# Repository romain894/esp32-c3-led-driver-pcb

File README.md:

# ESP32-C3 Wi-Fi LED driver

PCB based on an ESP32-C3 super mini to control LED:

  - Wi-Fi
  - Up to 6 PWM channels with MOSFET
  - 3 analog inputs
  - 24-12V to 5V step down chip
  - Extension to add an IR remote
  - Possibility to add I2C peripherals
  - An extra MOSFET on a non-PWM channel (e.g. to control an ATX power supply)

v1.0: tests in progress

Romain THOMAS 2024

## PCB views

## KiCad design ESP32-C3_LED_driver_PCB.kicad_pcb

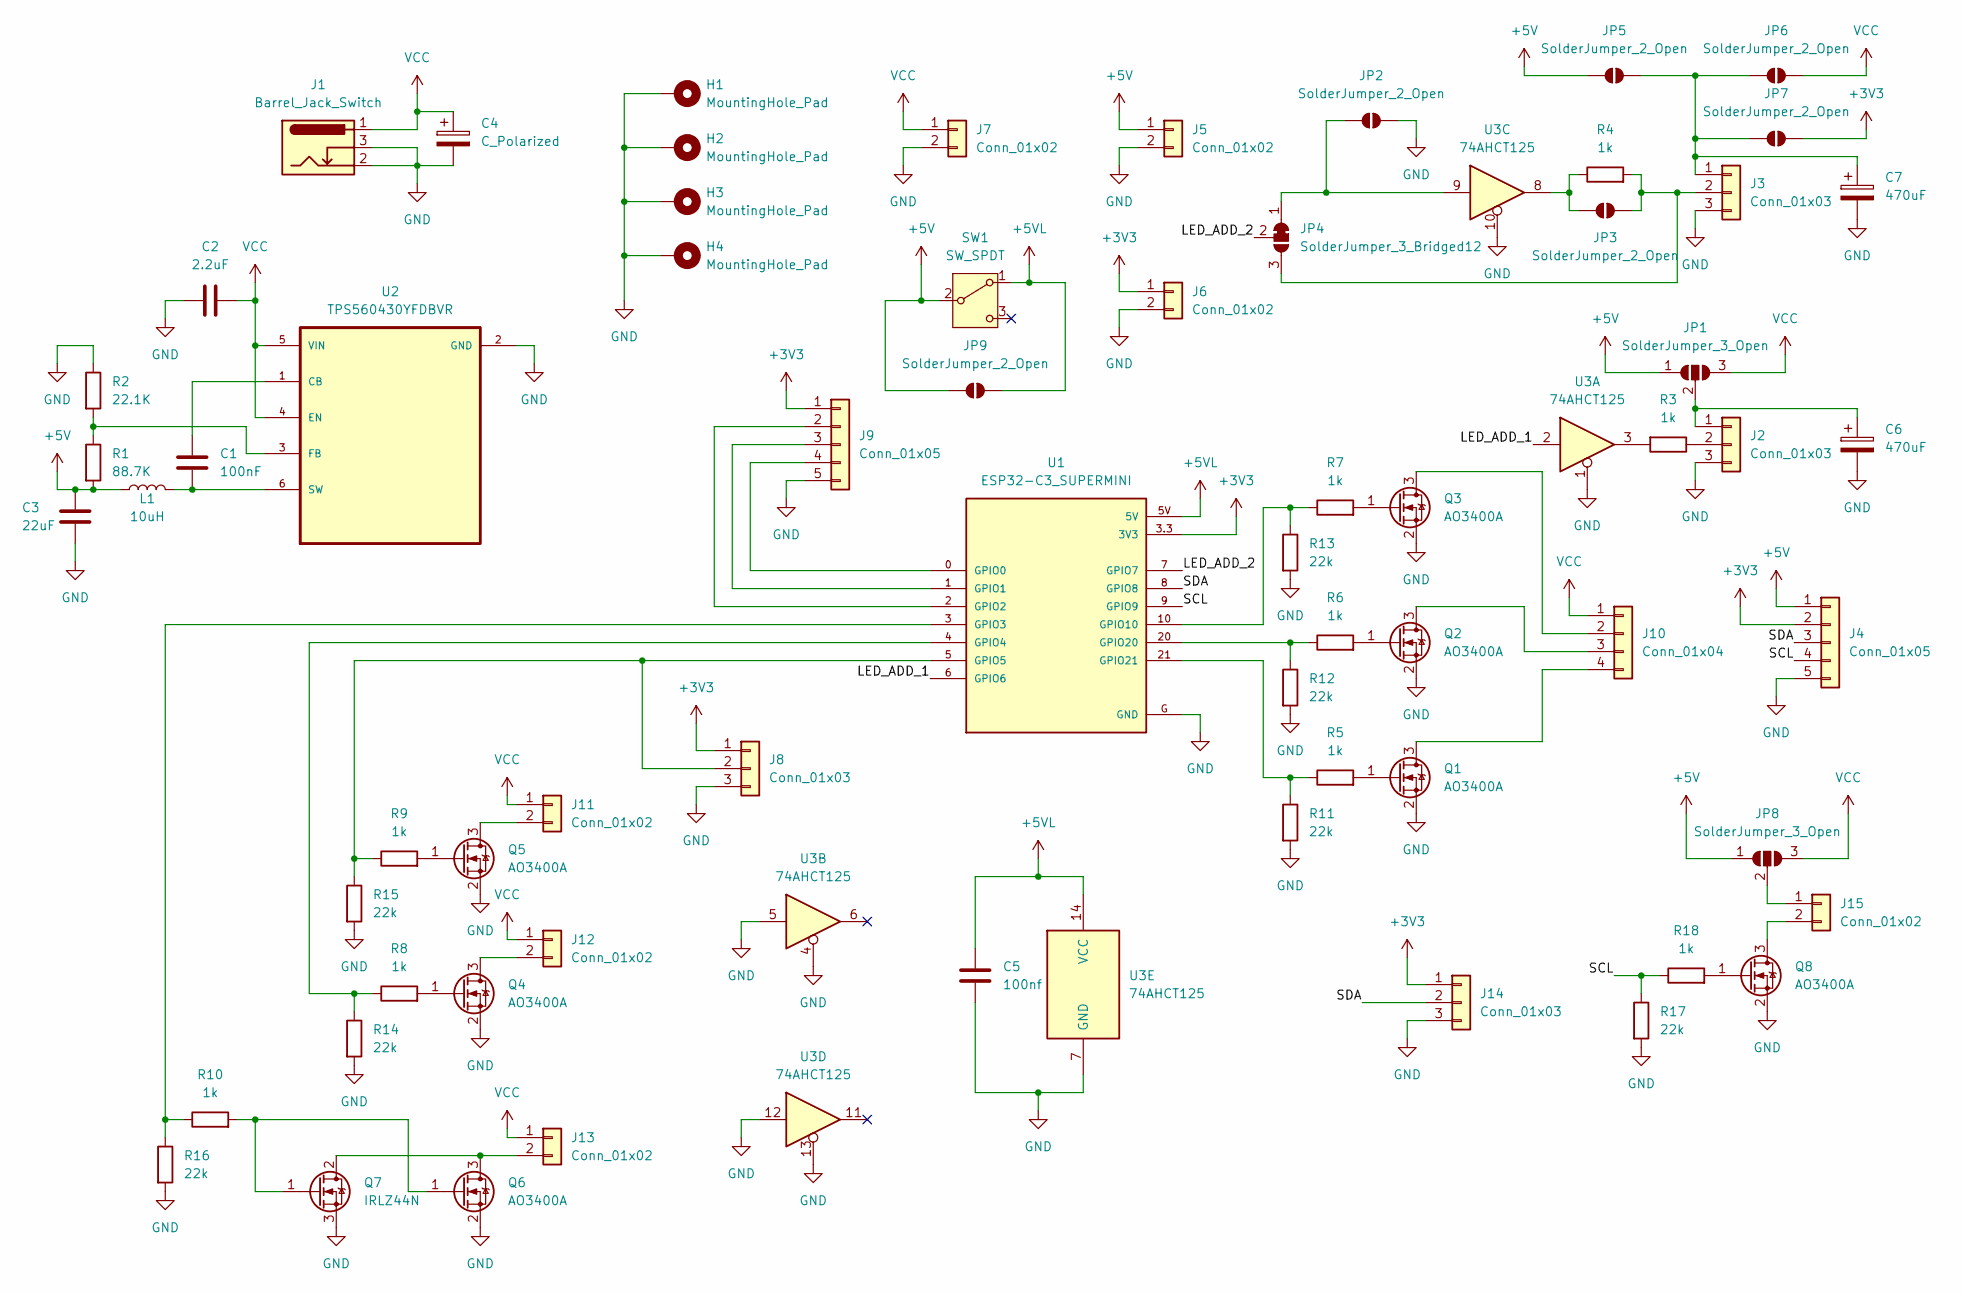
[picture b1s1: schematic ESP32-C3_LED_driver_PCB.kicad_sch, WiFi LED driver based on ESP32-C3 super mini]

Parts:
C1: 100nF; C_1206_3216Metric_Pad1.33x1.80mm_HandSolder
C2: 2.2uF; C_1206_3216Metric_Pad1.33x1.80mm_HandSolder
C3: 22uF; C_1206_3216Metric_Pad1.33x1.80mm_HandSolder
C4: C_Polarized; CP_Radial_D10.0mm_P2.50mm_P5.00mm
C5: 100nf; C_1206_3216Metric_Pad1.33x1.80mm_HandSolder
C6, C7: 470uF; CP_Radial_D10.0mm_P2.50mm_P5.00mm
H1, H2, H3, H4: MountingHole_Pad; MountingHole_3.5mm_Pad_Via
J1: Barrel_Jack_Switch; BarrelJack_Horizontal
J2, J3, J8, J14: Conn_01x03; JST_XH_B3B-XH-A_1x03_P2.50mm_Vertical
J4, J9: Conn_01x05; JST_XH_B5B-XH-A_1x05_P2.50mm_Vertical
J5, J6, J7, J11, J12, J13, J15: Conn_01x02; JST_XH_B2B-XH-A_1x02_P2.50mm_Vertical
J10: Conn_01x04; JST_XH_B4B-XH-A_1x04_P2.50mm_Vertical
JP1, JP8: SolderJumper_3_Open; SolderJumper-3_P1.3mm_Open_RoundedPad1.0x1.5mm
JP2, JP3, JP5, JP6, JP7, JP9: SolderJumper_2_Open; SolderJumper-2_P1.3mm_Open_RoundedPad1.0x1.5mm
JP4: SolderJumper_3_Bridged12; SolderJumper-3_P1.3mm_Bridged12_RoundedPad1.0x1.5mm
L1: 10uH; L_Chilisin_BMRA00040420
Q1, Q2, Q3, Q4, Q5, Q6, Q8: AO3400A; SOT-23
Q7: IRLZ44N; TO-220-3_Horizontal_TabDown
R1: 88.7K; R_1206_3216Metric_Pad1.30x1.75mm_HandSolder
R2: 22.1K; R_1206_3216Metric_Pad1.30x1.75mm_HandSolder
R3, R4, R5, R6, R7, R8, R9, R10, R18: 1k; R_1206_3216Metric_Pad1.30x1.75mm_HandSolder
R11, R12, R13, R14, R15, R16, R17: 22k; R_1206_3216Metric_Pad1.30x1.75mm_HandSolder
SW1: SW_SPDT; SW_Slide-03_Wuerth-WS-SLTV_10x2.5x6.4_P2.54mm
U1: ESP32-C3_SUPERMINI; MODULE_ESP32-C3_SUPERMINI
U2: TPS560430YFDBVR; SOT95P280X145-6N
U3: 74AHCT125; TSSOP-14_4.4x5mm_P0.65mm

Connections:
+3V3: J4.2, J6.1, J8.1, J9.1, J14.1, JP7.2 (B), U1.3.3 (3V3)
+5V: C3.1, J4.1, J5.1, JP1.1 (A), JP5.1 (A), JP8.1 (A), JP9.1 (A), L1.1, R1.2, SW1.2 (B)
+5VL: C5.1, JP9.2 (B), SW1.1 (A), U1.5V, U3.14 (VCC)
/LED_ADD_1: U1.6 (GPIO6), U3.2
/LED_ADD_2: JP4.2 (C), U1.7 (GPIO7)
/SCL: J4.4, R17.1, R18.1, U1.9 (GPIO9)
/SDA: J4.3, J14.2, U1.8 (GPIO8)
GND: C2.1, C3.2, C4.2, C5.2, C6.2, C7.2, H1.1, H2.1, H3.1, H4.1, J1.2, J1.3, J2.3, J3.3, J4.5, J5.2, J6.2, J7.2, J8.3, J9.5, J14.3, JP2.2 (B), Q1.2 (S), Q2.2 (S), Q3.2 (S), Q4.2 (S), Q5.2 (S), Q6.2 (S), Q7.3 (S), Q8.2 (S), R2.1, R11.2, R12.2, R13.2, R14.2, R15.2, R16.2, R17.2, U1.G (GND), U2.2 (GND), U3.1, U3.4, U3.5, U3.7 (GND), U3.10, U3.12, U3.13
unnamed: C6.1, J2.1, JP1.2 (C)
unnamed: J2.2, R3.1
unnamed: C7.1, J3.1, JP5.2 (B), JP6.1 (A), JP7.1 (A)
unnamed: J3.2, JP3.2 (B), JP4.3 (B), R4.2
unnamed: J8.2, R9.1, R15.1, U1.5 (GPIO5)
unnamed: J9.2, U1.2 (GPIO2)
unnamed: J9.3, U1.1 (GPIO1)
unnamed: J9.4, U1.0 (GPIO0)
unnamed: J10.2, Q3.3 (D)
unnamed: J10.3, Q2.3 (D)
unnamed: J10.4, Q1.3 (D)
unnamed: J11.2, Q5.3 (D)
unnamed: J12.2, Q4.3 (D)
unnamed: J13.2, Q6.3 (D), Q7.2 (D)
unnamed: J15.1, JP8.2 (C)
unnamed: J15.2, Q8.3 (D)
unnamed: JP2.1 (A), JP4.1 (A), U3.9
unnamed: JP3.1 (A), R4.1, U3.8
unnamed: Q1.1 (G), R5.2
unnamed: Q2.1 (G), R6.2
unnamed: Q3.1 (G), R7.2
unnamed: Q4.1 (G), R8.2
unnamed: Q5.1 (G), R9.2
unnamed: Q6.1 (G), Q7.1 (G), R10.2
unnamed: Q8.1 (G), R18.2
unnamed: R3.2, U3.3
unnamed: R10.1, R16.1, U1.3 (GPIO3)
unnamed: R8.1, R14.1, U1.4 (GPIO4)
unnamed: R7.1, R13.1, U1.10 (GPIO10)
unnamed: R6.1, R12.1, U1.20 (GPIO20)
unnamed: R5.1, R11.1, U1.21 (GPIO21)
unnamed: C1.1, U2.1 (CB)
unnamed: R1.1, R2.2, U2.3 (FB)
unnamed: C1.2, L1.2, U2.6 (SW)
VCC: C2.2, C4.1, J1.1, J7.1, J10.1, J11.1, J12.1, J13.1, JP1.3 (B), JP6.2 (B), JP8.3 (B), U2.4 (EN), U2.5 (VIN)

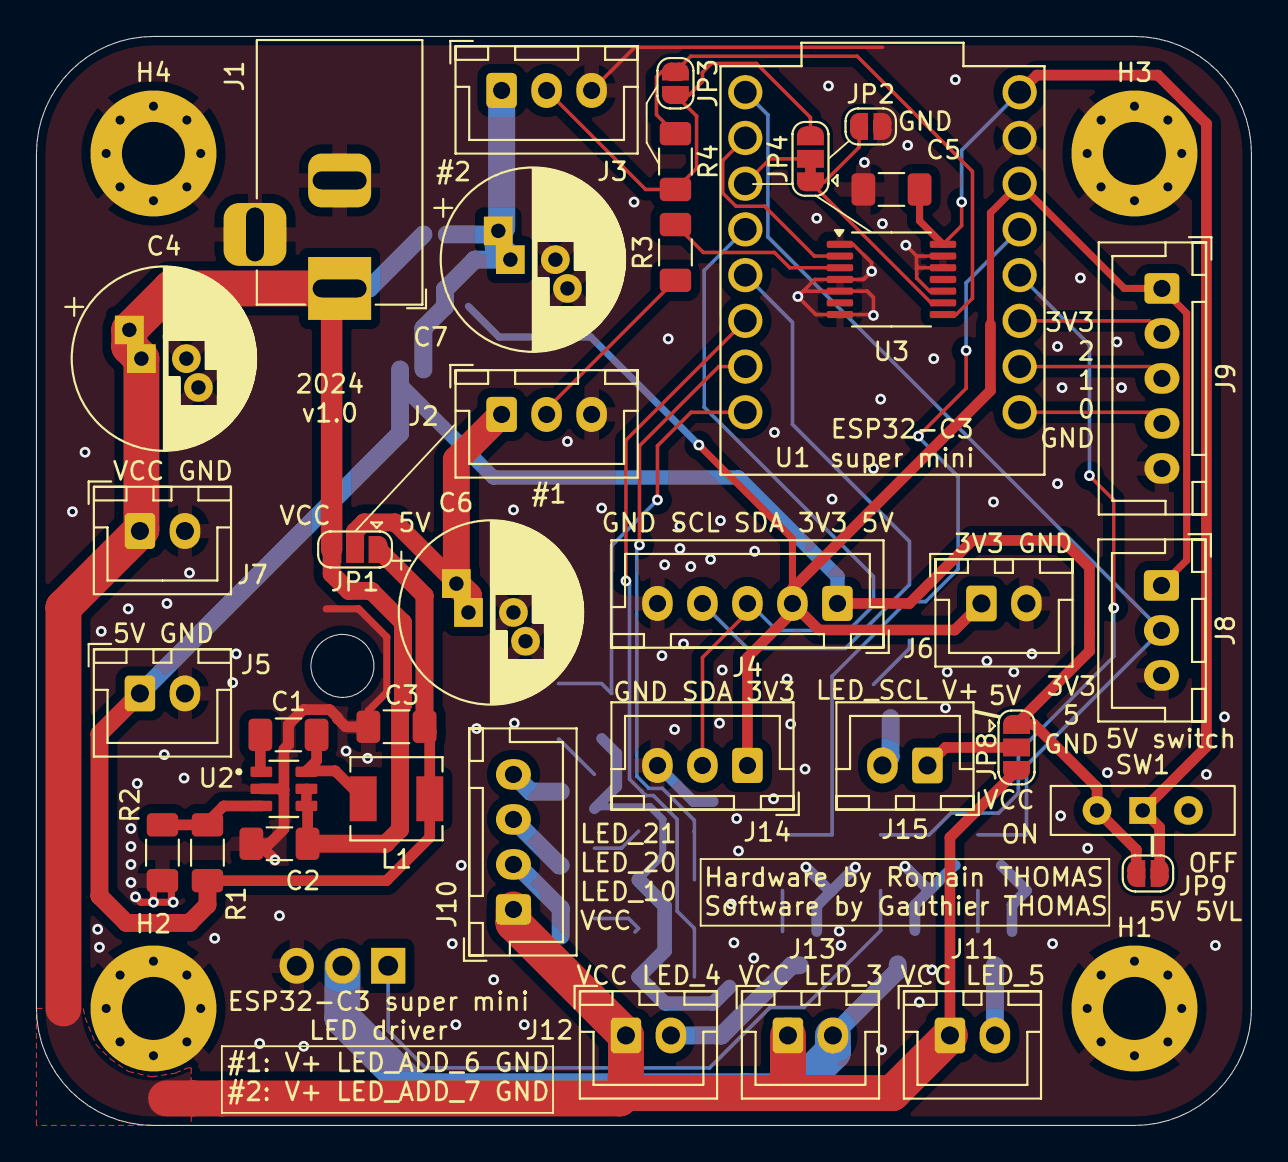
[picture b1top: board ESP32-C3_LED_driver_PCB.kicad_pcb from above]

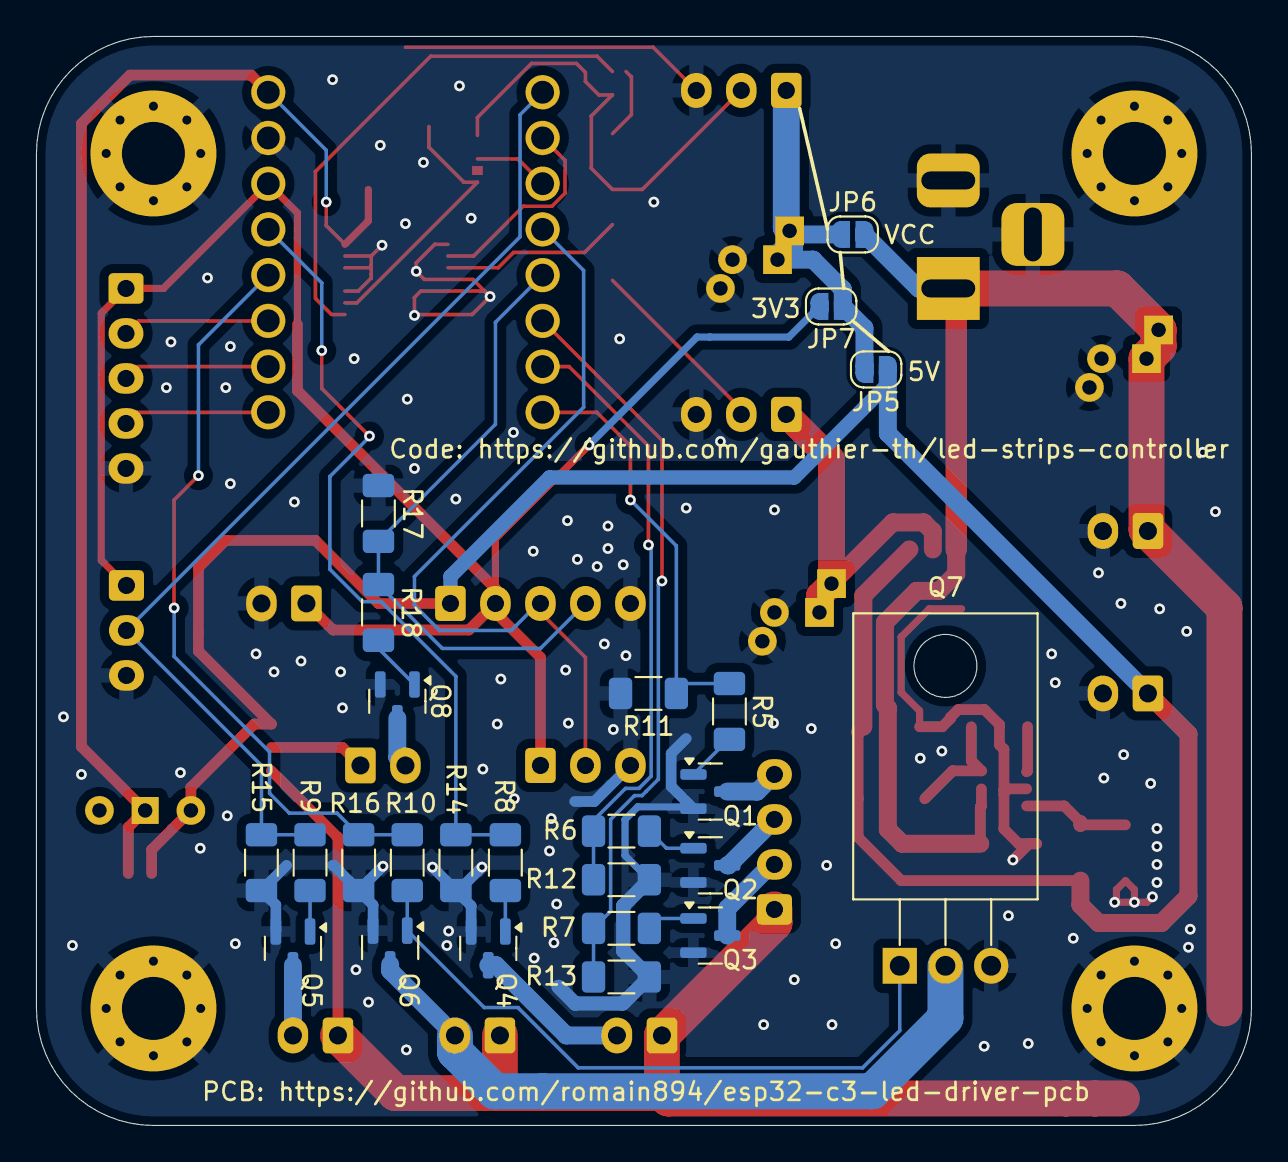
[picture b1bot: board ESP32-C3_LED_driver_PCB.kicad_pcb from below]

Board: 2 copper layers, 67.5 x 60.5 mm, 66 parts (25 on the bottom side), 43 nets.
